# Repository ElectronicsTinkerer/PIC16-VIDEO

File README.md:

# PIC16-VIDEO
Some PAL-composite video generation code for the PIC16

## Folder Structure
- [Code](./Code/) - Code examples and templates
- [PIC16F84DevBoard](./PIC16F84DevBoard/) - Files for video and serial breakout board

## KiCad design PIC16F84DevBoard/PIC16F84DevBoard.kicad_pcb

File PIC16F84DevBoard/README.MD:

# PIC16F84A Breakout/Dev Board

## Screenshot

## Features
- Onboard FTDI USB to UART IC, connected to `PORTA[0..1]`
- `PORTB` breakout header
- Reset button
- Composite video out (RCA) jack with mixing resistors

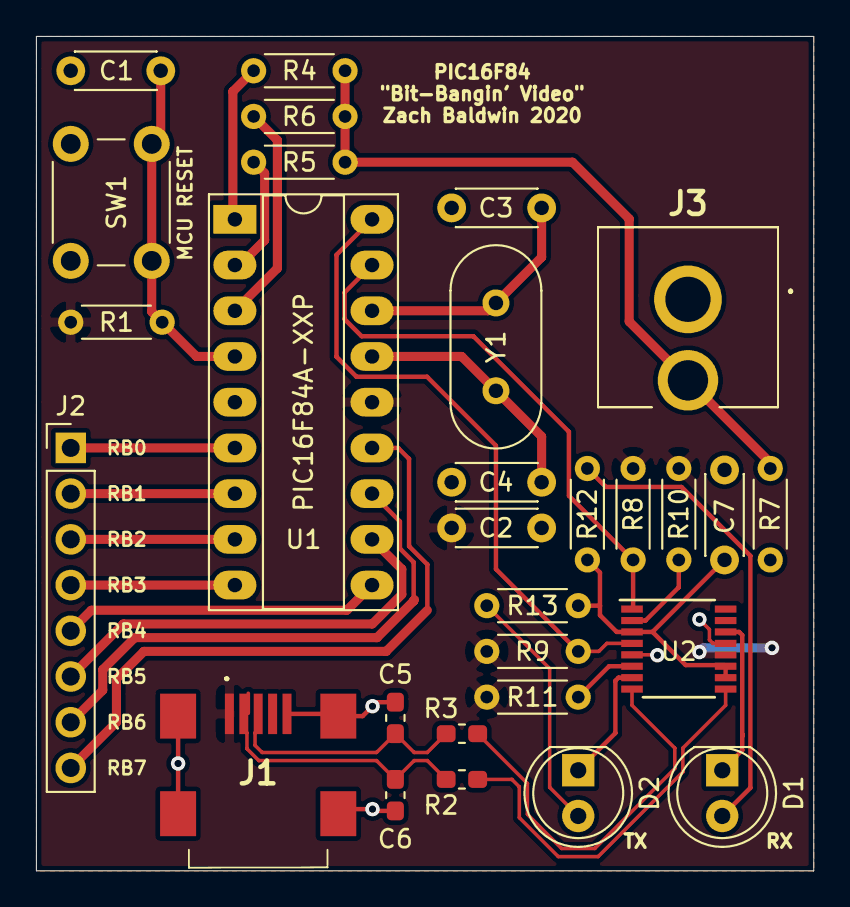
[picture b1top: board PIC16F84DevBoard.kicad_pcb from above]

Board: 2 copper layers, 43.2 x 46.4 mm, 29 parts (0 on the bottom side), 30 nets.

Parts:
C1, C2, C3, C4, C7: C; C_Disc_D4.3mm_W1.9mm_P5.00mm
C5, C6: 47pF; C_0603_1608Metric_Pad1.05x0.95mm_HandSolder
D1, D2: LED; LED_D5.0mm
J1: 10033526-N3222MLF; 10033526N3222MLF
J2: Conn_01x08_Male; PinHeader_1x08_P2.54mm_Vertical
J3: KLPX-0848A-2-Y; KLPX0848A2Y
R1, R8, R9, R10, R11: 10k; R_Axial_DIN0204_L3.6mm_D1.6mm_P5.08mm_Horizontal
R2, R3: 27; R_0603_1608Metric_Pad1.05x0.95mm_HandSolder
R4, R5, R6, R7: R; R_Axial_DIN0204_L3.6mm_D1.6mm_P5.08mm_Horizontal
R12, R13: 270; R_Axial_DIN0204_L3.6mm_D1.6mm_P5.08mm_Horizontal
SW1: SW_Push; SW_PUSH_6mm
U1: PIC16F84A-XXP; DIP-18_W7.62mm_Socket_LongPads
U2: FT230XS; SSOP-16_3.9x4.9mm_P0.635mm
Y1: Crystal; Crystal_HC49-U_Vertical

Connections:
+5V: C2.1, J1.1, R1.2, R8.2, R9.2, R10.2, R11.2, U1.14, U2.12
/DR_N: R2.1, U2.9
/DR_P: R3.1, U2.8
/D_N: C6.1, J1.2, R2.2
/D_P: C5.1, J1.3, R3.2
/RX: R9.1, U1.18, U2.4
/TX: R8.1, U1.17, U2.1
GND: C1.2, C2.2, C3.2, C4.2, C5.2, C6.2, C7.2, J1.5, J1.MP1, J1.MP2, J1.MP3, J1.MP4, J3.1, R7.1, SW1.1, U1.5, U2.5, U2.13
unnamed: C1.1, R1.1, SW1.2, U1.4
unnamed: C3.1, U1.16, Y1.1
unnamed: C4.1, U1.15, Y1.2
unnamed: C7.1, R12.1, R13.1, U2.3, U2.10, U2.11
unnamed: D1.1, U2.14
unnamed: D1.2, R12.2
unnamed: D2.1, U2.7
unnamed: D2.2, R13.2
unnamed: J2.1, U1.6
unnamed: J2.2, U1.7
unnamed: J2.3, U1.8
unnamed: J2.4, U1.9
unnamed: J2.5, U1.10
unnamed: J2.6, U1.11
unnamed: J2.7, U1.12
unnamed: J2.8, U1.13
unnamed: J3.2, R4.1, R5.1, R6.1, R7.2
unnamed: R4.2, U1.1
unnamed: R5.2, U1.2
unnamed: R6.2, U1.3
unnamed: R10.1, U2.2
unnamed: R11.1, U2.6

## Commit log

2021-01-09 Added board README
2021-01-09 Added instructions for assembling code
2021-01-10 Create LICENSE
2021-02-03 Added BRIK demo game
2021-03-15 Minor corrections
2022-06-02 SYNC and TEXT flowcharts
2022-06-02 Crop sync flowchart
